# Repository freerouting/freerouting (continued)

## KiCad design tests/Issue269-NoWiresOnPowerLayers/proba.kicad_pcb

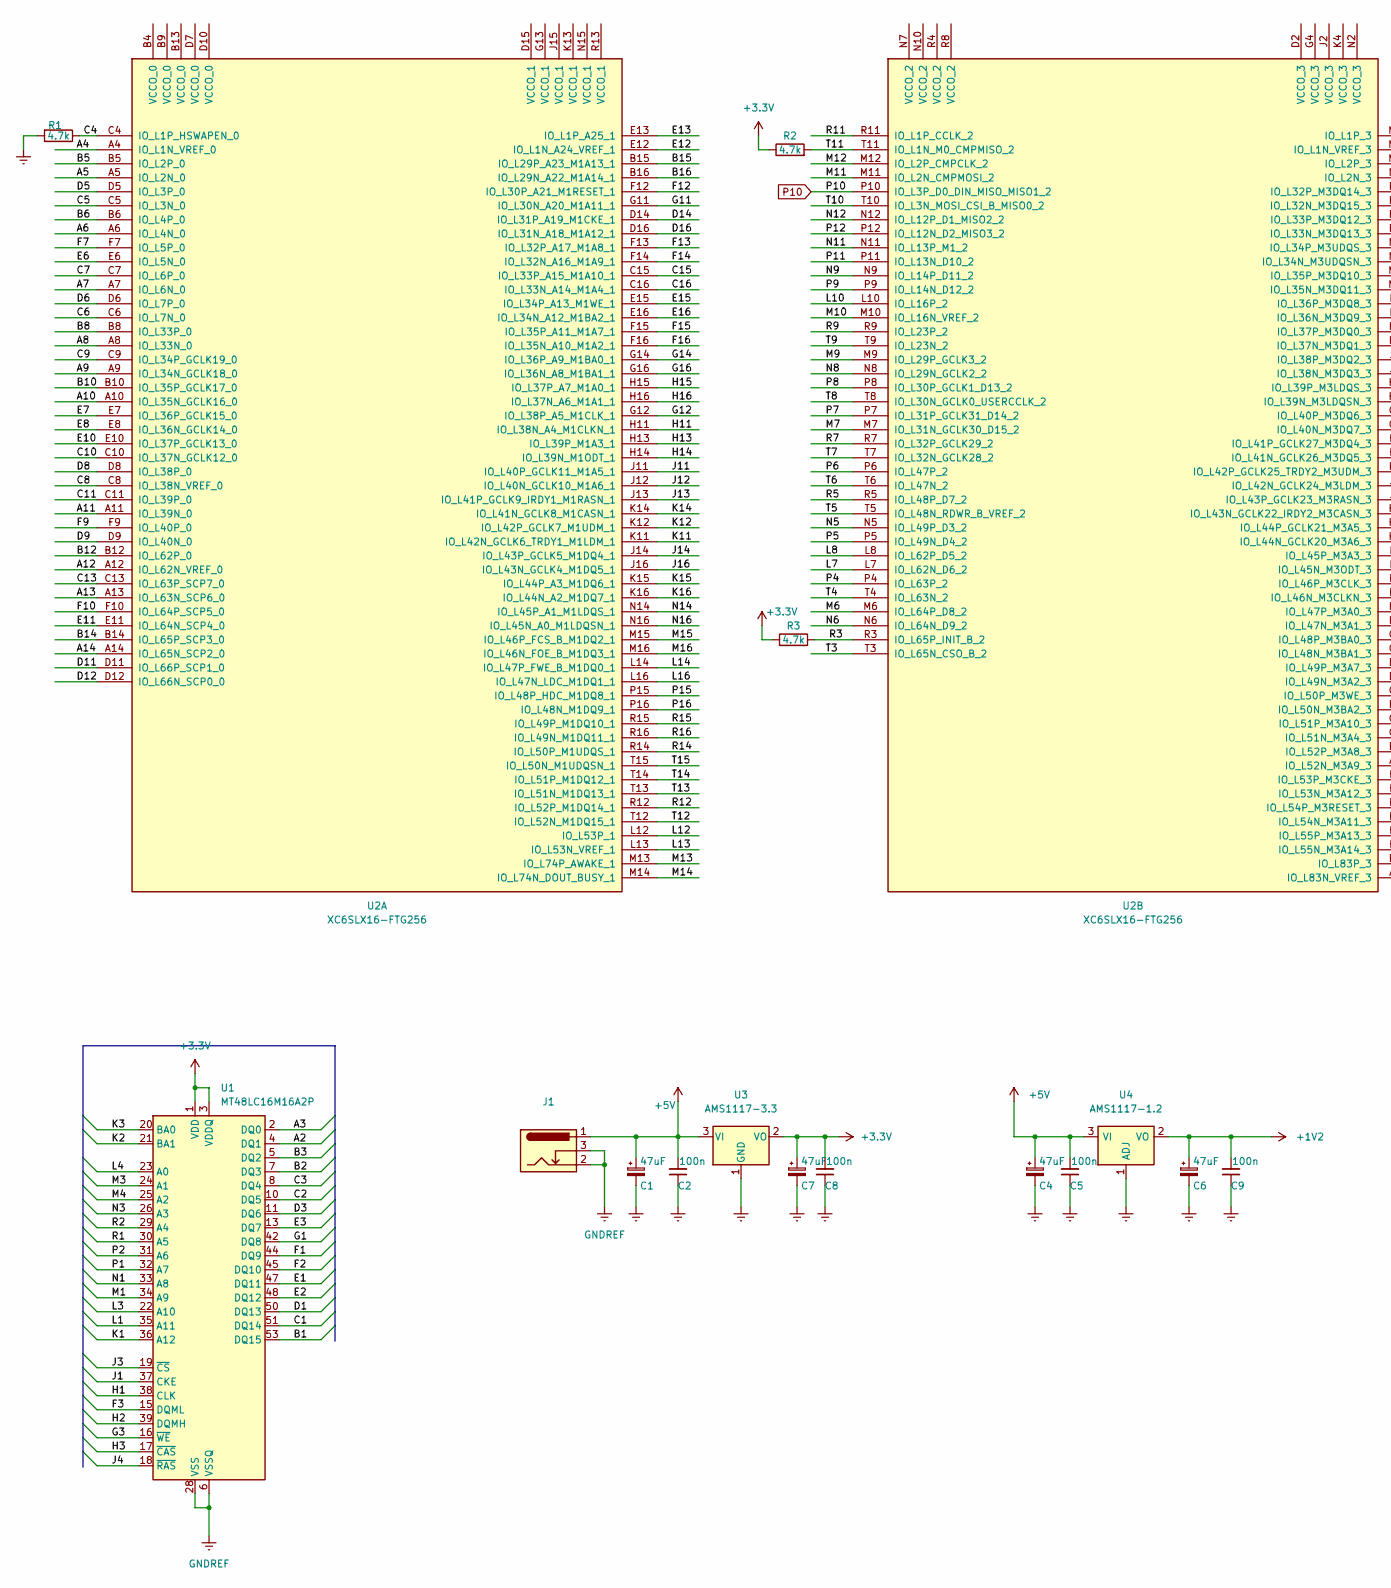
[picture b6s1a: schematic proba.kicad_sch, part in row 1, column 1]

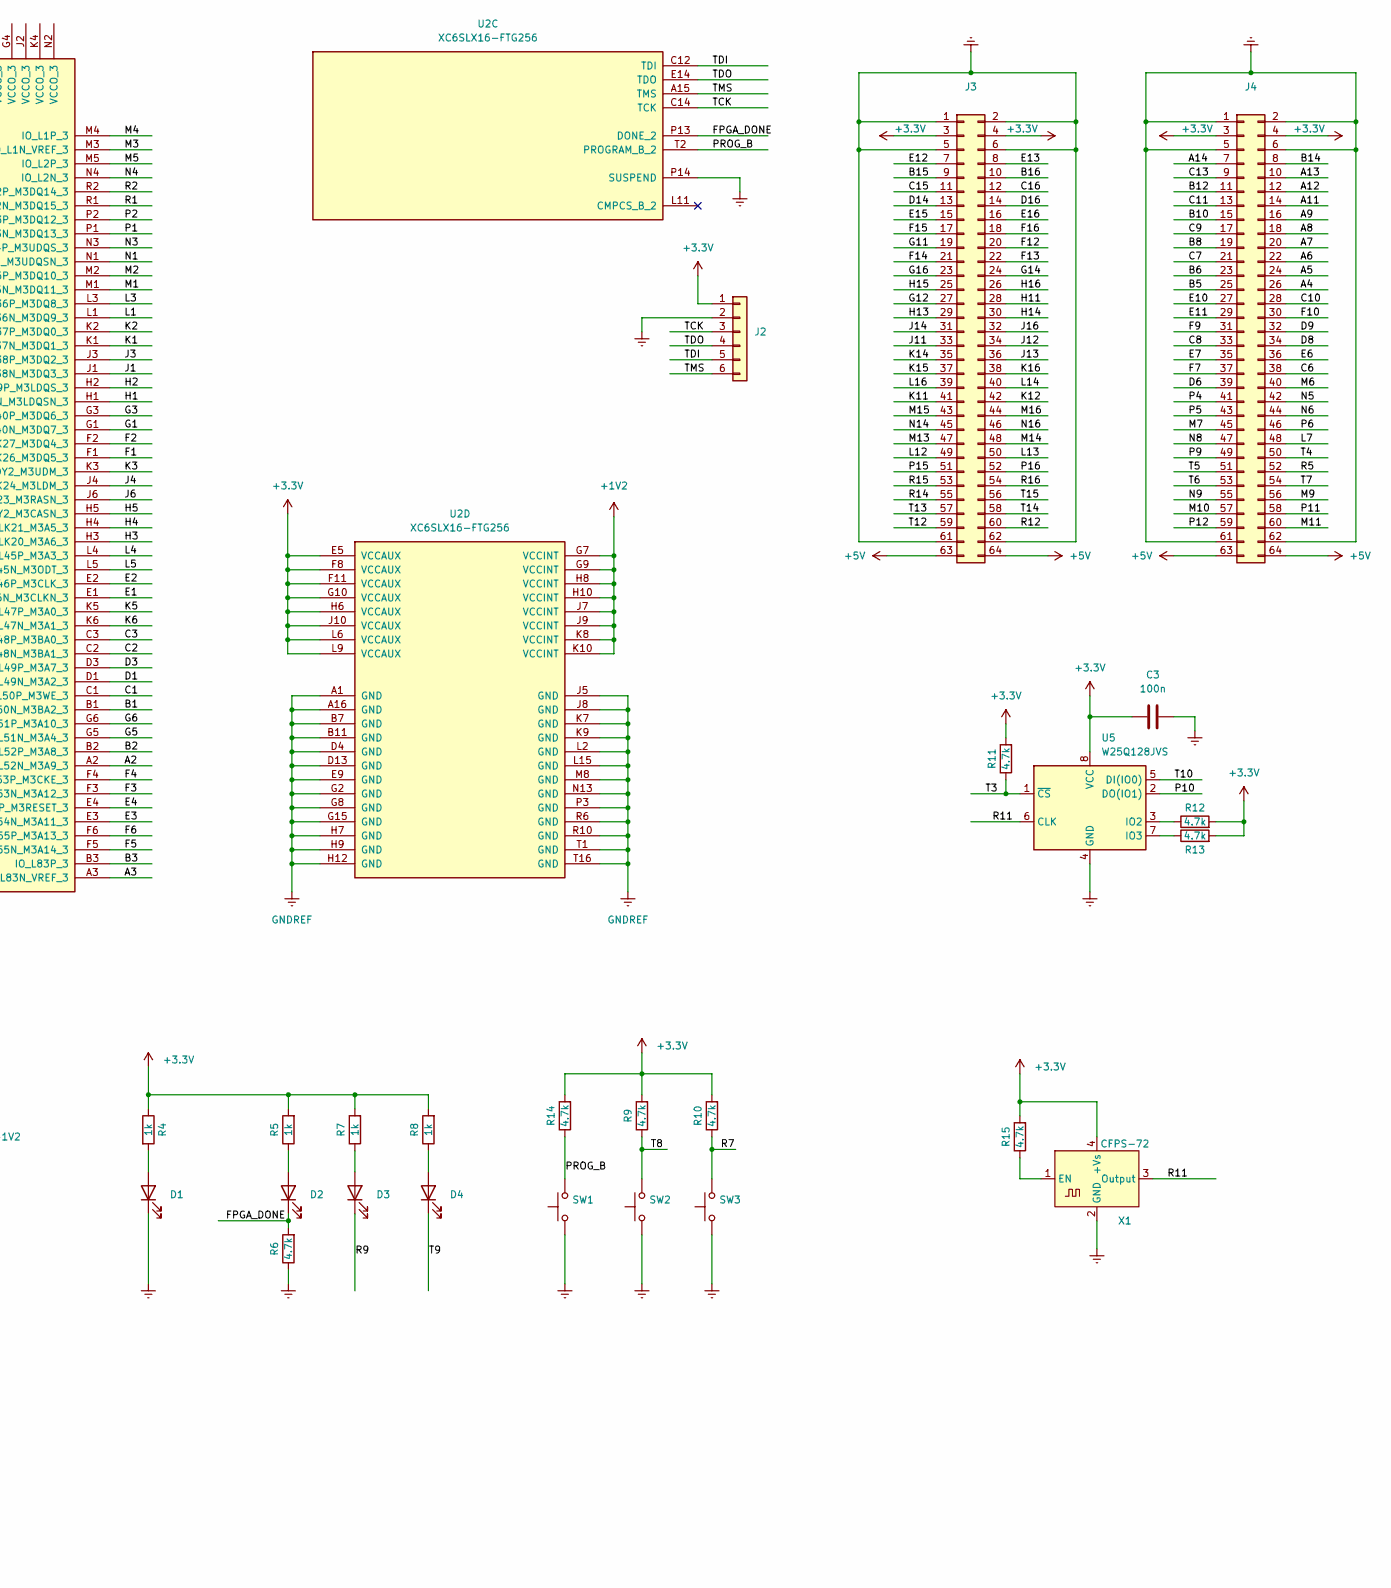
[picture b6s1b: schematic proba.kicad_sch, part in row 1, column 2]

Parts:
C1, C4, C6, C7: 47uF; C_1206_3216Metric
C2, C3, C5, C8, C9: 100n; C_1206_3216Metric
D1, D2, D3, D4: LED; LED_0805_2012Metric_Pad1.15x1.40mm_HandSolder
J1: Barrel_Jack_Switch; BarrelJack_Horizontal
J2: Conn_01x06; PinHeader_1x06_P2.54mm_Vertical
J3, J4: Conn_02x32_Odd_Even; PinHeader_2x32_P2.54mm_Vertical
R1, R2, R3, R6, R9, R10, R11, R12, R13, R14, R15: 4.7k; R_0805_2012Metric_Pad1.20x1.40mm_HandSolder
R4, R5, R7, R8: 1k; R_0805_2012Metric_Pad1.20x1.40mm_HandSolder
SW1, SW2, SW3: SW_Push; smd_push
U1: MT48LC16M16A2P; TSOP-II-54_22.2x10.16mm_P0.8mm
U2: XC6SLX16-FTG256; BGA-256_17.0x17.0mm_Layout16x16_P1.0mm_Ball0.5mm_Pad0.4mm_N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
U3: AMS1117-3.3; SOT-223-3_TabPin2
U4: AMS1117-1.2; SOT-223-3_TabPin2
U5: W25Q128JVS; SOIC-8_5.23x5.23mm_P1.27mm
X1: CFPS-72; Oscillator_SMD_IQD_IQXO70-4Pin_7.5x5.0mm

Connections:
+1V2: C6.1, C9.2, U2.G7 (VCCINT), U2.G9 (VCCINT), U2.H8 (VCCINT), U2.H10 (VCCINT), U2.J7 (VCCINT), U2.J9 (VCCINT), U2.K8 (VCCINT), U2.K10 (VCCINT), U4.2 (VO)
+3V3: C3.1, C7.1, C8.2, J2.1, J3.3, J3.4, J4.3, J4.4, R2.1, R3.1, R4.1, R5.2, R7.2, R8.2, R9.2, R10.2, R11.2, R12.2, R13.2, R14.2, R15.2, U1.1 (VDD), U1.3 (VDDQ), U1.9 (VDDQ), U1.14 (VDD), U1.27 (VDD), U1.43 (VDDQ), U1.49 (VDDQ), U2.E5 (VCCAUX), U2.F8 (VCCAUX), U2.F11 (VCCAUX), U2.G10 (VCCAUX), U2.H6 (VCCAUX), U2.J10 (VCCAUX), U2.L6 (VCCAUX), U2.L9 (VCCAUX), U3.2 (VO), U5.8 (VCC), X1.4 (+Vs)
+5V: C1.1, C2.2, C4.1, C5.2, J1.1, J3.63, J3.64, J4.63, J4.64, U3.3 (VI), U4.3 (VI)
/A2: U1.4 (DQ1), U2.A2 (IO_L52N_M3A9_3)
/A3: U1.2 (DQ0), U2.A3 (IO_L83N_VREF_3)
/A4: J4.26, U2.A4 (IO_L1N_VREF_0)
/A5: J4.24, U2.A5 (IO_L2N_0)
/A6: J4.22, U2.A6 (IO_L4N_0)
/A7: J4.20, U2.A7 (IO_L6N_0)
/A8: J4.18, U2.A8 (IO_L33N_0)
/A9: J4.16, U2.A9 (IO_L34N_GCLK18_0)
/A10: U2.A10 (IO_L35N_GCLK16_0)
/A11: J4.14, U2.A11 (IO_L39N_0)
/A12: J4.12, U2.A12 (IO_L62N_VREF_0)
/A13: J4.10, U2.A13 (IO_L63N_SCP6_0)
/A14: J4.7, U2.A14 (IO_L65N_SCP2_0)
/B1: U1.53 (DQ15), U2.B1 (IO_L50N_M3BA2_3)
/B2: U1.7 (DQ3), U2.B2 (IO_L52P_M3A8_3)
/B3: U1.5 (DQ2), U2.B3 (IO_L83P_3)
/B5: J4.25, U2.B5 (IO_L2P_0)
/B6: J4.23, U2.B6 (IO_L4P_0)
/B8: J4.19, U2.B8 (IO_L33P_0)
/B10: J4.15, U2.B10 (IO_L35P_GCLK17_0)
/B12: J4.11, U2.B12 (IO_L62P_0)
/B14: J4.8, U2.B14 (IO_L65P_SCP3_0)
/B15: J3.9, U2.B15 (IO_L29P_A23_M1A13_1)
/B16: J3.10, U2.B16 (IO_L29N_A22_M1A14_1)
/C1: U1.51 (DQ14), U2.C1 (IO_L50P_M3WE_3)
/C2: U1.10 (DQ5), U2.C2 (IO_L48N_M3BA1_3)
/C3: U1.8 (DQ4), U2.C3 (IO_L48P_M3BA0_3)
/C4: R1.1, U2.C4 (IO_L1P_HSWAPEN_0)
/C5: U2.C5 (IO_L3N_0)
/C6: J4.38, U2.C6 (IO_L7N_0)
/C7: J4.21, U2.C7 (IO_L6P_0)
/C8: J4.33, U2.C8 (IO_L38N_VREF_0)
/C9: J4.17, U2.C9 (IO_L34P_GCLK19_0)
/C10: J4.28, U2.C10 (IO_L37N_GCLK12_0)
/C11: J4.13, U2.C11 (IO_L39P_0)
/C13: J4.9, U2.C13 (IO_L63P_SCP7_0)
/C15: J3.11, U2.C15 (IO_L33P_A15_M1A10_1)
/C16: J3.12, U2.C16 (IO_L33N_A14_M1A4_1)
/D1: U1.50 (DQ13), U2.D1 (IO_L49N_M3A2_3)
/D3: U1.11 (DQ6), U2.D3 (IO_L49P_M3A7_3)
/D5: U2.D5 (IO_L3P_0)
/D6: J4.39, U2.D6 (IO_L7P_0)
/D8: J4.34, U2.D8 (IO_L38P_0)
/D9: J4.32, U2.D9 (IO_L40N_0)
/D11: U2.D11 (IO_L66P_SCP1_0)
/D12: U2.D12 (IO_L66N_SCP0_0)
/D14: J3.13, U2.D14 (IO_L31P_A19_M1CKE_1)
/D16: J3.14, U2.D16 (IO_L31N_A18_M1A12_1)
/E1: U1.47 (DQ11), U2.E1 (IO_L46N_M3CLKN_3)
/E2: U1.48 (DQ12), U2.E2 (IO_L46P_M3CLK_3)
/E3: U1.13 (DQ7), U2.E3 (IO_L54N_M3A11_3)
/E4: U2.E4 (IO_L54P_M3RESET_3)
/E6: J4.36, U2.E6 (IO_L5N_0)
/E7: J4.35, U2.E7 (IO_L36P_GCLK15_0)
/E8: U2.E8 (IO_L36N_GCLK14_0)
/E10: J4.27, U2.E10 (IO_L37P_GCLK13_0)
/E11: J4.29, U2.E11 (IO_L64N_SCP4_0)
/E12: J3.7, U2.E12 (IO_L1N_A24_VREF_1)
/E13: J3.8, U2.E13 (IO_L1P_A25_1)
/E15: J3.15, U2.E15 (IO_L34P_A13_M1WE_1)
/E16: J3.16, U2.E16 (IO_L34N_A12_M1BA2_1)
/F1: U1.44 (DQ9), U2.F1 (IO_L41N_GCLK26_M3DQ5_3)
/F2: U1.45 (DQ10), U2.F2 (IO_L41P_GCLK27_M3DQ4_3)
/F3: U1.15 (DQML), U2.F3 (IO_L53N_M3A12_3)
/F4: U2.F4 (IO_L53P_M3CKE_3)
/F5: U2.F5 (IO_L55N_M3A14_3)
/F6: U2.F6 (IO_L55P_M3A13_3)
/F7: J4.37, U2.F7 (IO_L5P_0)
/F9: J4.31, U2.F9 (IO_L40P_0)
/F10: J4.30, U2.F10 (IO_L64P_SCP5_0)
/F12: J3.20, U2.F12 (IO_L30P_A21_M1RESET_1)
/F13: J3.22, U2.F13 (IO_L32P_A17_M1A8_1)
/F14: J3.21, U2.F14 (IO_L32N_A16_M1A9_1)
/F15: J3.17, U2.F15 (IO_L35P_A11_M1A7_1)
/F16: J3.18, U2.F16 (IO_L35N_A10_M1A2_1)
/FPGA_DONE: D2.1 (K), R6.2, U2.P13 (DONE_2)
/G1: U1.42 (DQ8), U2.G1 (IO_L40N_M3DQ7_3)
/G3: U1.16 (~WE), U2.G3 (IO_L40P_M3DQ6_3)
/G5: U2.G5 (IO_L51N_M3A4_3)
/G6: U2.G6 (IO_L51P_M3A10_3)
/G11: J3.19, U2.G11 (IO_L30N_A20_M1A11_1)
/G12: J3.27, U2.G12 (IO_L38P_A5_M1CLK_1)
/G14: J3.24, U2.G14 (IO_L36P_A9_M1BA0_1)
/G16: J3.23, U2.G16 (IO_L36N_A8_M1BA1_1)
/H1: U1.38 (CLK), U2.H1 (IO_L39N_M3LDQSN_3)
/H2: U1.39 (DQMH), U2.H2 (IO_L39P_M3LDQS_3)
/H3: U1.17 (~CAS), U2.H3 (IO_L44N_GCLK20_M3A6_3)
/H4: U2.H4 (IO_L44P_GCLK21_M3A5_3)
/H5: U2.H5 (IO_L43N_GCLK22_IRDY2_M3CASN_3)
/H11: J3.28, U2.H11 (IO_L38N_A4_M1CLKN_1)
/H13: J3.29, U2.H13 (IO_L39P_M1A3_1)
/H14: J3.30, U2.H14 (IO_L39N_M1ODT_1)
/H15: J3.25, U2.H15 (IO_L37P_A7_M1A0_1)
/H16: J3.26, U2.H16 (IO_L37N_A6_M1A1_1)
/J1: U1.37 (CKE), U2.J1 (IO_L38N_M3DQ3_3)
/J3: U1.19 (~CS), U2.J3 (IO_L38P_M3DQ2_3)
/J4: U1.18 (~RAS), U2.J4 (IO_L42N_GCLK24_M3LDM_3)
/J6: U2.J6 (IO_L43P_GCLK23_M3RASN_3)
/J11: J3.33, U2.J11 (IO_L40P_GCLK11_M1A5_1)
/J12: J3.34, U2.J12 (IO_L40N_GCLK10_M1A6_1)
/J13: J3.36, U2.J13 (IO_L41P_GCLK9_IRDY1_M1RASN_1)
/J14: J3.31, U2.J14 (IO_L43P_GCLK5_M1DQ4_1)
/J16: J3.32, U2.J16 (IO_L43N_GCLK4_M1DQ5_1)
/K1: U1.36 (A12), U2.K1 (IO_L37N_M3DQ1_3)
/K2: U1.21 (BA1), U2.K2 (IO_L37P_M3DQ0_3)
/K3: U1.20 (BA0), U2.K3 (IO_L42P_GCLK25_TRDY2_M3UDM_3)
/K5: U2.K5 (IO_L47P_M3A0_3)
/K6: U2.K6 (IO_L47N_M3A1_3)
/K11: J3.41, U2.K11 (IO_L42N_GCLK6_TRDY1_M1LDM_1)
/K12: J3.42, U2.K12 (IO_L42P_GCLK7_M1UDM_1)
/K14: J3.35, U2.K14 (IO_L41N_GCLK8_M1CASN_1)
/K15: J3.37, U2.K15 (IO_L44P_A3_M1DQ6_1)
/K16: J3.38, U2.K16 (IO_L44N_A2_M1DQ7_1)
/L1: U1.35 (A11), U2.L1 (IO_L36N_M3DQ9_3)
/L3: U1.22 (A10), U2.L3 (IO_L36P_M3DQ8_3)
/L4: U1.23 (A0), U2.L4 (IO_L45P_M3A3_3)
/L5: U2.L5 (IO_L45N_M3ODT_3)
/L7: J4.48, U2.L7 (IO_L62N_D6_2)
/L8: U2.L8 (IO_L62P_D5_2)
/L10: U2.L10 (IO_L16P_2)
/L12: J3.49, U2.L12 (IO_L53P_1)
/L13: J3.50, U2.L13 (IO_L53N_VREF_1)
/L14: J3.40, U2.L14 (IO_L47P_FWE_B_M1DQ0_1)
/L16: J3.39, U2.L16 (IO_L47N_LDC_M1DQ1_1)
/M1: U1.34 (A9), U2.M1 (IO_L35N_M3DQ11_3)
/M2: U2.M2 (IO_L35P_M3DQ10_3)
/M3: U1.24 (A1), U2.M3 (IO_L1N_VREF_3)
/M4: U1.25 (A2), U2.M4 (IO_L1P_3)
/M5: U2.M5 (IO_L2P_3)
/M6: J4.40, U2.M6 (IO_L64P_D8_2)
/M7: J4.45, U2.M7 (IO_L31N_GCLK30_D15_2)
/M9: J4.56, U2.M9 (IO_L29P_GCLK3_2)
/M10: J4.57, U2.M10 (IO_L16N_VREF_2)
/M11: J4.60, U2.M11 (IO_L2N_CMPMOSI_2)
/M12: U2.M12 (IO_L2P_CMPCLK_2)
/M13: J3.47, U2.M13 (IO_L74P_AWAKE_1)
/M14: J3.48, U2.M14 (IO_L74N_DOUT_BUSY_1)
/M15: J3.43, U2.M15 (IO_L46P_FCS_B_M1DQ2_1)
/M16: J3.44, U2.M16 (IO_L46N_FOE_B_M1DQ3_1)
/N1: U1.33 (A8), U2.N1 (IO_L34N_M3UDQSN_3)
/N3: U1.26 (A3), U2.N3 (IO_L34P_M3UDQS_3)
/N4: U2.N4 (IO_L2N_3)
/N5: J4.42, U2.N5 (IO_L49P_D3_2)
/N6: J4.44, U2.N6 (IO_L64N_D9_2)
/N8: J4.47, U2.N8 (IO_L29N_GCLK2_2)
/N9: J4.55, U2.N9 (IO_L14P_D11_2)
/N11: U2.N11 (IO_L13P_M1_2)
/N12: U2.N12 (IO_L12P_D1_MISO2_2)
/N14: J3.45, U2.N14 (IO_L45P_A1_M1LDQS_1)
/N16: J3.46, U2.N16 (IO_L45N_A0_M1LDQSN_1)
/P1: U1.32 (A7), U2.P1 (IO_L33N_M3DQ13_3)
/P2: U1.31 (A6), U2.P2 (IO_L33P_M3DQ12_3)
/P4: J4.41, U2.P4 (IO_L63P_2)
/P5: J4.43, U2.P5 (IO_L49N_D4_2)
/P6: J4.46, U2.P6 (IO_L47P_2)
/P7: U2.P7 (IO_L31P_GCLK31_D14_2)
/P8: U2.P8 (IO_L30P_GCLK1_D13_2)
/P9: J4.49, U2.P9 (IO_L14N_D12_2)
/P11: J4.58, U2.P11 (IO_L13N_D10_2)
/P12: J4.59, U2.P12 (IO_L12N_D2_MISO3_2)
/P15: J3.51, U2.P15 (IO_L48P_HDC_M1DQ8_1)
/P16: J3.52, U2.P16 (IO_L48N_M1DQ9_1)
/PROG_B: R14.1, SW1.2, U2.T2 (PROGRAM_B_2)
/R1: U1.30 (A5), U2.R1 (IO_L32N_M3DQ15_3)
/R2: U1.29 (A4), U2.R2 (IO_L32P_M3DQ14_3)
/R3: R3.2, U2.R3 (IO_L65P_INIT_B_2)
/R5: J4.52, U2.R5 (IO_L48P_D7_2)
/R7: R10.1, SW3.2, U2.R7 (IO_L32P_GCLK29_2)
/R9: D3.1 (K), U2.R9 (IO_L23P_2)
/R11: U2.R11 (IO_L1P_CCLK_2), U5.6 (CLK), X1.3 (Output)
/R12: J3.60, U2.R12 (IO_L52P_M1DQ14_1)
/R14: J3.55, U2.R14 (IO_L50P_M1UDQS_1)
/R15: J3.53, U2.R15 (IO_L49P_M1DQ10_1)
/R16: J3.54, U2.R16 (IO_L49N_M1DQ11_1)
/T3: R11.1, U2.T3 (IO_L65N_CSO_B_2), U5.1 (~CS)
/T4: J4.50, U2.T4 (IO_L63N_2)
/T5: J4.51, U2.T5 (IO_L48N_RDWR_B_VREF_2)
/T6: J4.53, U2.T6 (IO_L47N_2)
/T7: J4.54, U2.T7 (IO_L32N_GCLK28_2)
/T8: R9.1, SW2.2, U2.T8 (IO_L30N_GCLK0_USERCCLK_2)
/T9: D4.1 (K), U2.T9 (IO_L23N_2)
/T10: U2.T10 (IO_L3N_MOSI_CSI_B_MISO0_2), U5.5 (DI(IO0))
/T11: R2.2, U2.T11 (IO_L1N_M0_CMPMISO_2)
/T12: J3.59, U2.T12 (IO_L52N_M1DQ15_1)
/T13: J3.57, U2.T13 (IO_L51N_M1DQ13_1)
/T14: J3.58, U2.T14 (IO_L51P_M1DQ12_1)
/T15: J3.56, U2.T15 (IO_L50N_M1UDQSN_1)
/TCK: J2.3, U2.C14 (TCK)
/TDI: J2.5, U2.C12 (TDI)
/TDO: J2.4, U2.E14 (TDO)
/TMS: J2.6, U2.A15 (TMS)
GNDREF: C1.2, C2.1, C3.2, C4.2, C5.1, C6.2, C7.2, C8.1, C9.1, D1.1 (K), J1.2, J1.3, J2.2, J3.1, J3.2, J3.5, J3.6, J3.61, J3.62, J4.1, J4.2, J4.5, J4.6, J4.61, J4.62, R1.2, R6.1, SW1.1, SW2.1, SW3.1, U1.6 (VSSQ), U1.12 (VSSQ), U1.28 (VSS), U1.41 (VSS), U1.46 (VSSQ), U1.52 (VSSQ), U1.54 (VSS), U2.A1 (GND), U2.A16 (GND), U2.B7 (GND), U2.B11 (GND), U2.D4 (GND), U2.D13 (GND), U2.E9 (GND), U2.G2 (GND), U2.G8 (GND), U2.G15 (GND), U2.H7 (GND), U2.H9 (GND), U2.H12 (GND), U2.J5 (GND), U2.J8 (GND), U2.K7 (GND), U2.K9 (GND), U2.L2 (GND), U2.L15 (GND), U2.M8 (GND), U2.N13 (GND), U2.P3 (GND), U2.P14 (SUSPEND), U2.R6 (GND), U2.R10 (GND), U2.T1 (GND), U2.T16 (GND), U3.1 (GND), U4.1 (ADJ), U5.4 (GND), X1.2 (GND)
unnamed: D1.2 (A), R4.2
unnamed: D2.2 (A), R5.1
unnamed: D3.2 (A), R7.1
unnamed: D4.2 (A), R8.1
unnamed: R12.1, U5.3 (IO2)
unnamed: R13.1, U5.7 (IO3)
unnamed: R15.1, X1.1 (EN)
P10: U2.P10 (IO_L3P_D0_DIN_MISO_MISO1_2), U5.2 (DO(IO1))

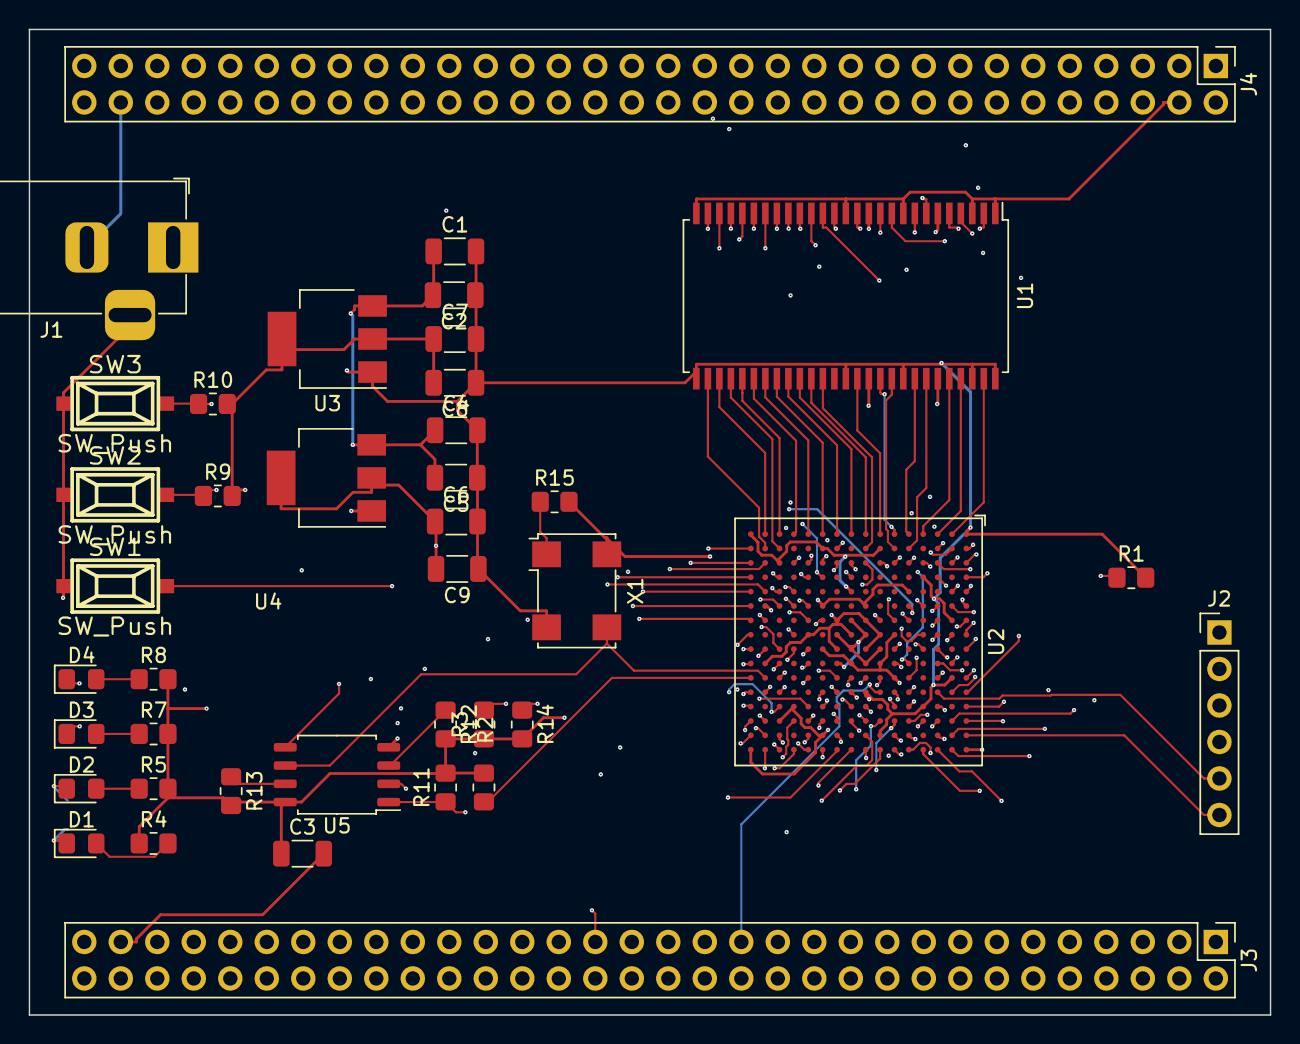
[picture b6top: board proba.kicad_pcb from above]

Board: 4 copper layers, 86.4 x 68.6 mm, 41 parts (1 on the bottom side), 175 nets.

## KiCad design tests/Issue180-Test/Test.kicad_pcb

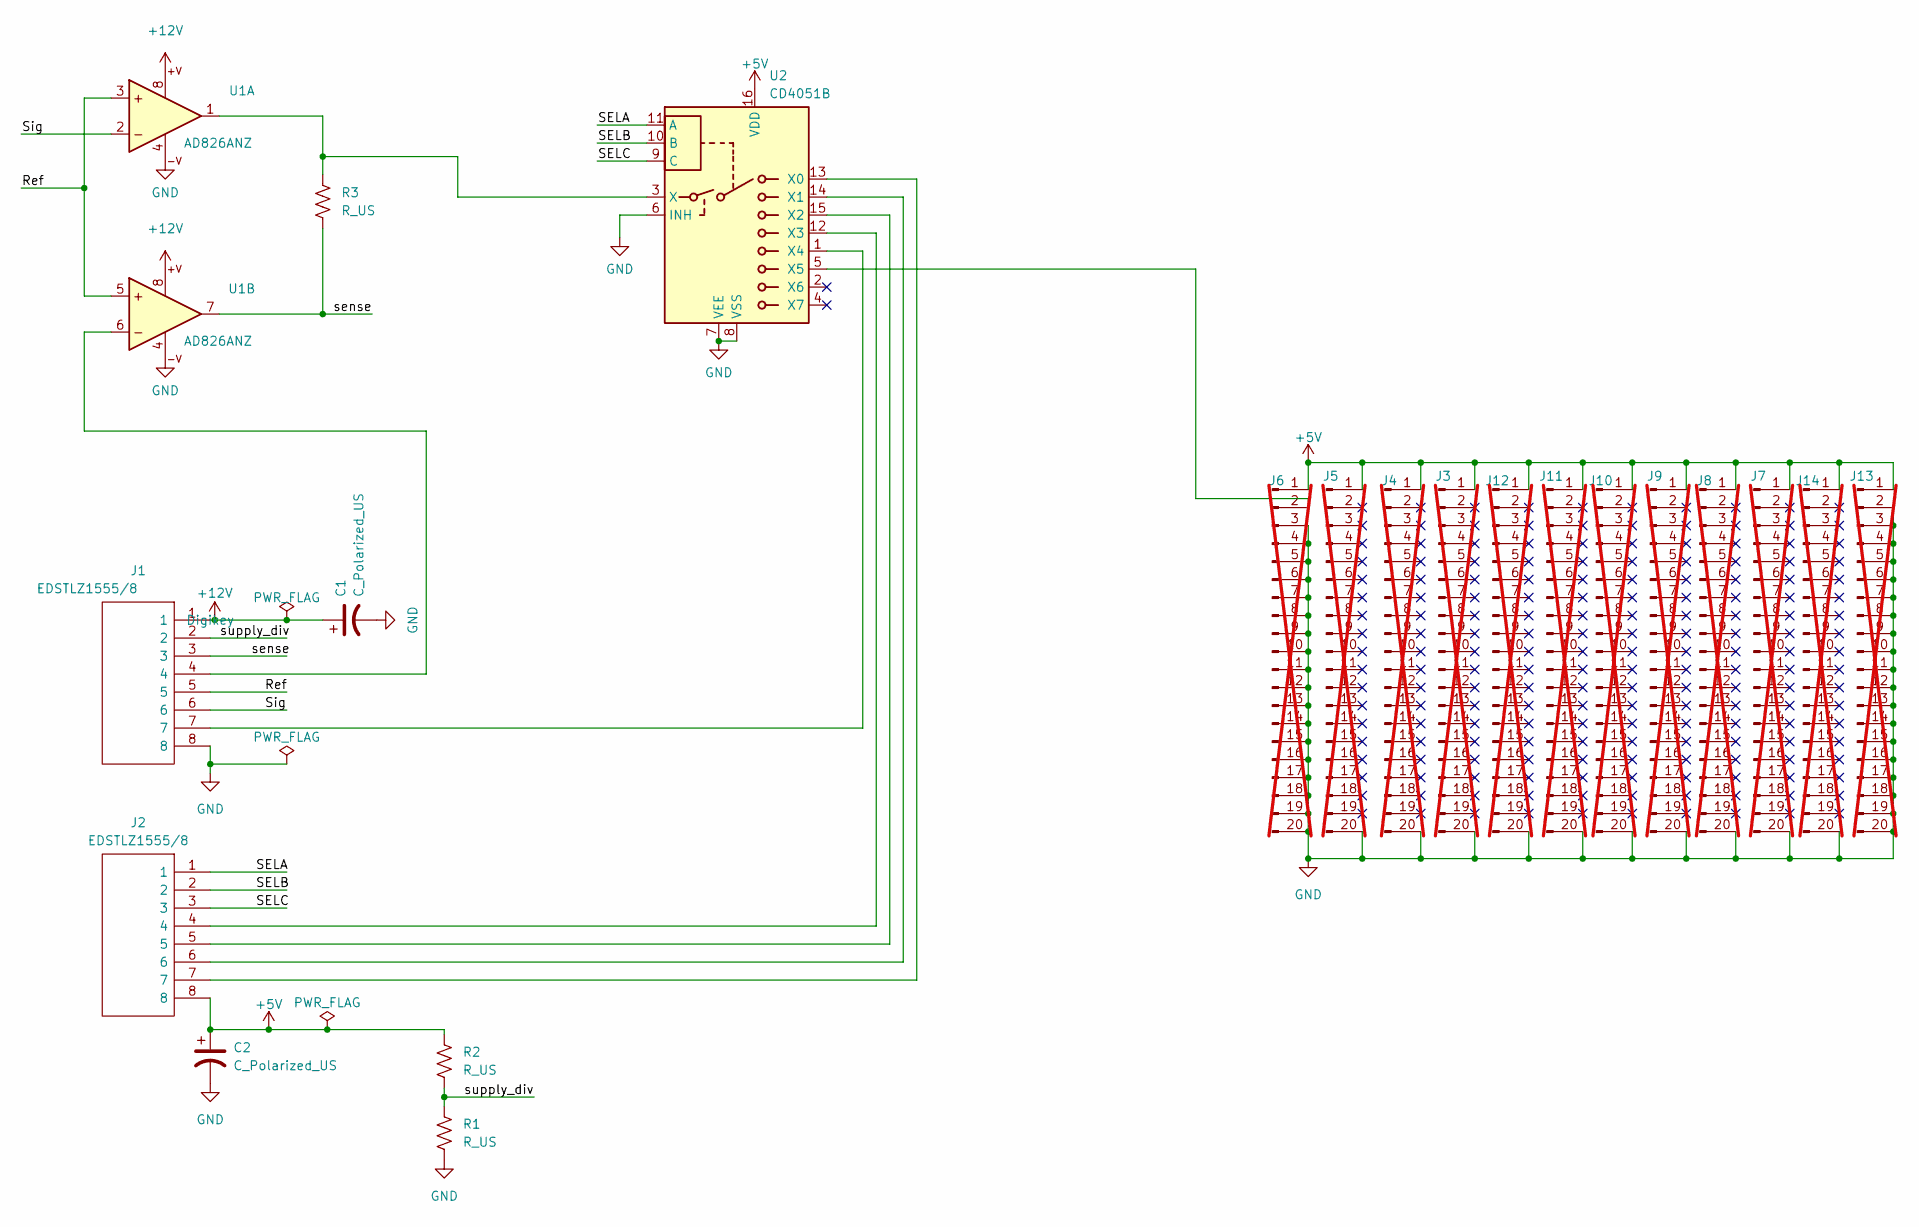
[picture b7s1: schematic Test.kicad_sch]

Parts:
C1, C2: C_Polarized_US; CP_Radial_D5.0mm_P2.50mm
J1, J2: EDSTLZ1555/8; CONN-TH_EDSTLZ1555-8
J3, J4, J5, J6, J7, J8, J9, J10, J11, J12, J13, J14: Conn_01x20_Pin; SIP-20_PERF; not fitted
R1, R2, R3: R_US; R_Axial_DIN0207_L6.3mm_D2.5mm_P11.43mm_Horizontal_0.25W
U1: AD826ANZ; DIP-8_W7.62mm_LongPads
U2: CD4051B; DIP-16_W7.62mm_LongPads

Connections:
+5V: C2.1, J2.8, J3.1, J4.1, J5.1, J6.1, J7.1, J8.1, J9.1, J10.1, J11.1, J12.1, J13.1, J14.1, R2.1, U2.16 (VDD)
+12V: C1.1, J1.1, U1.8 (V+)
/Ref: J1.5, U1.3 (+), U1.5 (+)
/SELA: J2.1, U2.11 (A)
/SELB: J2.2, U2.10 (B)
/SELC: J2.3, U2.9 (C)
/Sig: J1.6, U1.2 (-)
/sense: J1.3, R3.2, U1.7
/supply_div: J1.2, R1.1, R2.2
GND: C1.2, C2.2, J1.8, J3.20, J4.20, J5.20, J6.3, J6.4, J6.5, J6.6, J6.7, J6.8, J6.9, J6.10, J6.11, J6.12, J6.13, J6.14, J6.15, J6.16, J6.17, J6.18, J6.19, J6.20, J7.20, J8.20, J9.20, J10.20, J11.20, J12.20, J13.2, J13.3, J13.4, J13.5, J13.6, J13.7, J13.8, J13.9, J13.10, J13.11, J13.12, J13.13, J13.14, J13.15, J13.16, J13.17, J13.18, J13.19, J13.20, J14.20, R1.2, U1.4 (V-), U2.6 (INH), U2.7 (VEE), U2.8 (VSS)
unnamed: J6.2, U2.5 (X5)
unnamed: J1.4, U1.6 (-)
unnamed: J2.7, U2.13 (X0)
unnamed: J2.6, U2.14 (X1)
unnamed: J2.5, U2.15 (X2)
unnamed: J2.4, U2.12 (X3)
unnamed: J1.7, U2.1 (X4)
unnamed: R3.1, U1.1, U2.3 (X)

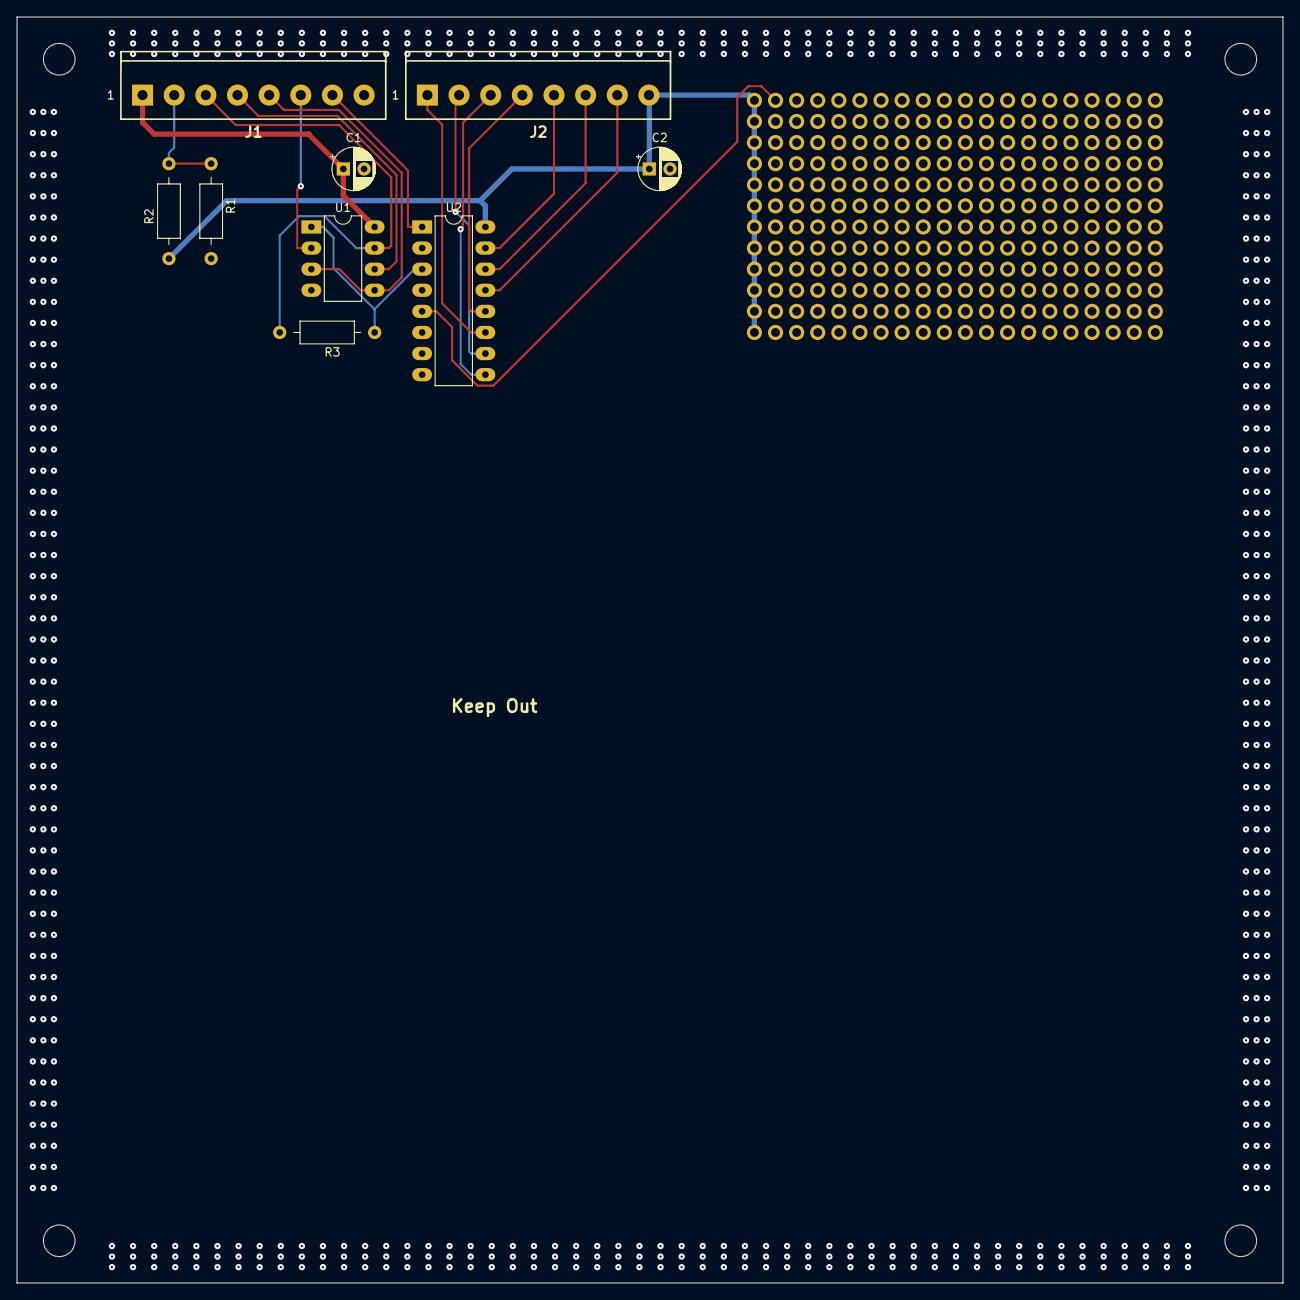
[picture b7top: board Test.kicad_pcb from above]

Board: 4 copper layers, 152.4 x 152.4 mm, 25 parts (0 on the bottom side), 18 nets.

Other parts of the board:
MT1, MT2, MT3, MT4: MountingHole_NPTH_150mil

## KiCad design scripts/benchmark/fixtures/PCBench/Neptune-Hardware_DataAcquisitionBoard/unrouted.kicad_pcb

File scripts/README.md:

# Freerouting daemon & progress update (#313)

## Summary

The 'scripts' folder contains the following tools:

- Bash Script `freeroutingd` (Freerouting Daemon) to automatically make a fake X11 desktop to run headless freerouting.
- C++ program `freeroutingp` (Freerouting Progress) translate the log of freerouting to `stderr` stream by pipe.

You need to set the following environment variables:
`JAVA` - path to the JRE executable what freerouting uses (optional)
`ARG_GUI` - set it to "TRUE" to enable GUI (for OS like Windows)

Now we only can write `{"status": "startRoute"}`, `{"status": "routeProgress"}`, `{"status": "routeResult"}`, `{"status": "startOptimize"}` and `{"status": "optimizeResult"}`.

Bugs:

- `{"status": "routeProgress"}` doesn't work in my computer. Because no message `Saving xxx...` sent. Please update log system to output real information in routing, like pass number, etc.
- Sometimes the freerouting will push a dialog like "There is a snapshot. Would you like use this snapshot?". Headless cannot cancel this dialog.
- Sometimes there will be a net exception. But no effect for auto-routing.

like:

```
java.util.concurrent.CompletionException: java.net.ConnectException
        at java.base/java.util.concurrent.CompletableFuture.encodeRelay(CompletableFuture.java:368)
        at java.base/java.util.concurrent.CompletableFuture.completeRelay(CompletableFuture.java:377)
        at java.base/java.util.concurrent.CompletableFuture$UniCompose.tryFire(CompletableFuture.java:1152)
        at java.base/java.util.concurrent.CompletableFuture.postComplete(CompletableFuture.java:510)
        at java.base/java.util.concurrent.CompletableFuture$AsyncSupply.run(CompletableFuture.java:1773)
        at java.base/java.util.concurrent.ThreadPoolExecutor.runWorker(ThreadPoolExecutor.java:1144)
        at java.base/java.util.concurrent.ThreadPoolExecutor$Worker.run(ThreadPoolExecutor.java:642)
        at java.base/java.lang.Thread.run(Thread.java:1583)
Caused by: java.net.ConnectException
        at java.net.http/jdk.internal.net.http.common.Utils.toConnectException(Utils.java:1028)
        at java.net.http/jdk.internal.net.http.PlainHttpConnection.connectAsync(PlainHttpConnection.java:227)
        at java.net.http/jdk.internal.net.http.PlainHttpConnection.checkRetryConnect(PlainHttpConnection.java:280)
        at java.net.http/jdk.internal.net.http.PlainHttpConnection.lambda$connectAsync$2(PlainHttpConnection.java:238)
        at java.base/java.util.concurrent.CompletableFuture.uniHandle(CompletableFuture.java:934)
        at java.base/java.util.concurrent.CompletableFuture$UniHandle.tryFire(CompletableFuture.java:911)
        ... 5 more
Caused by: java.nio.channels.ClosedChannelException
        at java.base/sun.nio.ch.SocketChannelImpl.ensureOpen(SocketChannelImpl.java:202)
        at java.base/sun.nio.ch.SocketChannelImpl.beginConnect(SocketChannelImpl.java:786)
        at java.base/sun.nio.ch.SocketChannelImpl.connect(SocketChannelImpl.java:874)
        at java.net.http/jdk.internal.net.http.PlainHttpConnection.lambda$connectAsync$1(PlainHttpConnection.java:210)
        at java.base/java.security.AccessController.doPrivileged(AccessController.java:571)
        at java.net.http/jdk.internal.net.http.PlainHttpConnection.connectAsync(PlainHttpConnection.java:212)
        ... 9 more
```

## freeroutingp

For now, `freeroutingp` is just for test. 

We must update the log system to provide more information, and `freeroutingp` will be more useful.

If we can convert .ses to EasyEDA's API format, we can compatible with it. (See #311)

(For now, I can't, but maybe I can develop a electron plugin for EasyEDA, and it also can make the same effect)

And thanks for @leoheck to provide this idea in #241.

## How to compile the C++ code

1. Boot up your Linux or Windows Subsystem for Linux (WSL)

2. Install compiler tools

```
sudo apt update
sudo apt install build-essential git
```

3. Clone the Freerouting repo (if you haven't already)

```
git clone https://github.com/freerouting/freerouting.git
```

3. Navigate to your Freerouting source directory and its scripts subdirectory

4. Run the compiler

```
make
```

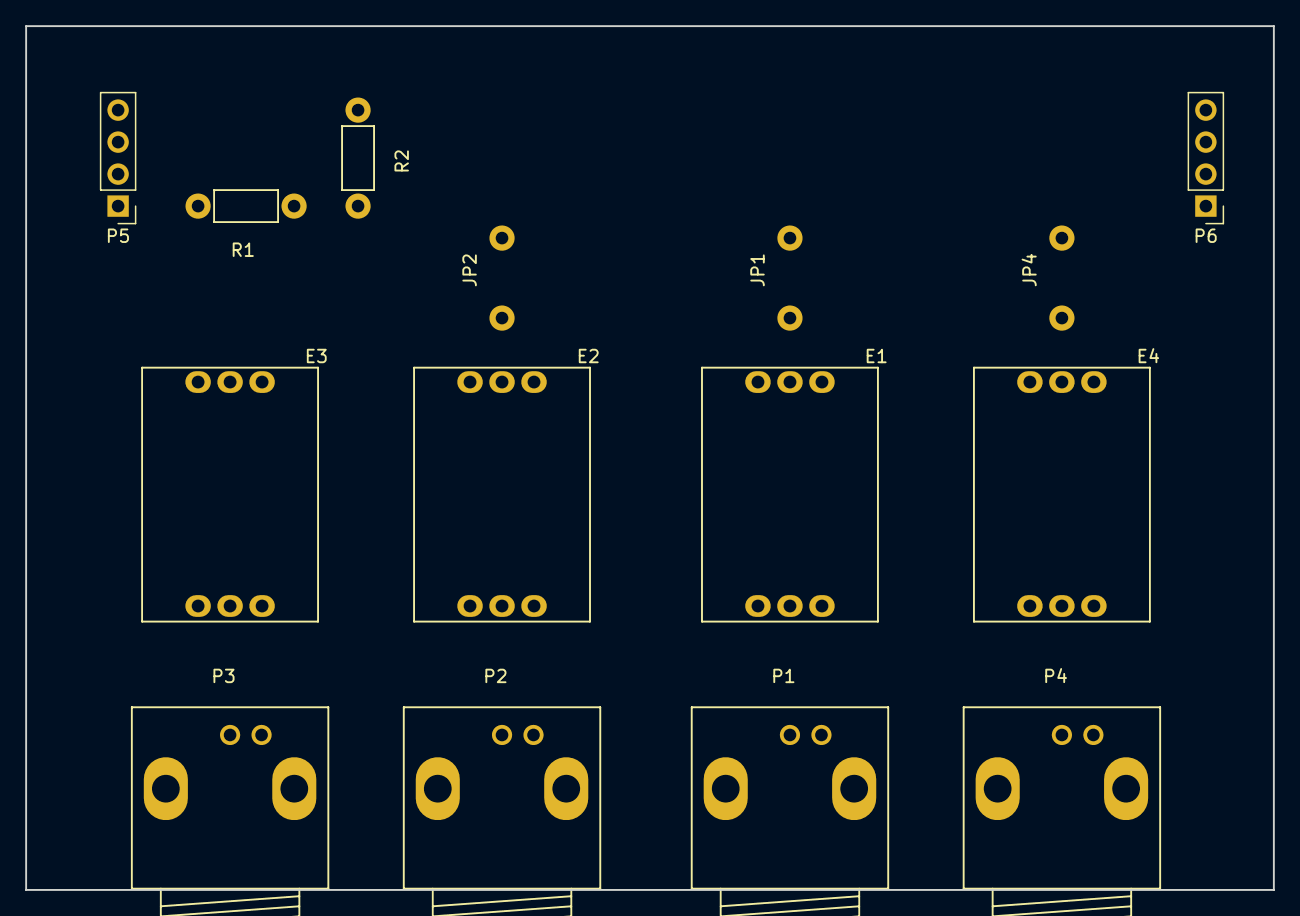
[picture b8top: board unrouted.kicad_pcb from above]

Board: 2 copper layers, 99.1 x 68.6 mm, 15 parts (0 on the bottom side), 15 nets, no tracks yet.

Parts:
E1, E3, E4: phEZO
E2: DO_EZO; phEZO
JP1, JP2, JP4: JUMPER; Jumper_6.35mm
P1, P2, P3, P4: BNC; BNC_Socket_TYCO-AMP
P5, P6: CONN_01X04; Pin_Header_Straight_1x04_Pitch2.54mm
R1, R2: 12K; Resistor_Horizontal_RM7mm

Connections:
+5V: E1.6, E2.6, E3.6, E4.6, P5.1, P6.1, R1.2, R2.2
A4: E3.2, JP1.2, JP2.2, JP4.2, P5.3, P6.3, R1.1
A5: E1.3, E2.3, E3.3, E4.3, P5.4, P6.4, R2.1
GND: E1.1, E2.1, E3.1, E4.1, P5.2, P6.2
unnamed: E1.2, JP1.1
unnamed: E1.4, P1.2
unnamed: E1.5, P1.1
unnamed: E2.2, JP2.1
unnamed: E2.4, P2.2
unnamed: E2.5, P2.1
unnamed: E3.4, P3.2
unnamed: E3.5, P3.1
unnamed: E4.2, JP4.1
unnamed: E4.4, P4.2
unnamed: E4.5, P4.1
